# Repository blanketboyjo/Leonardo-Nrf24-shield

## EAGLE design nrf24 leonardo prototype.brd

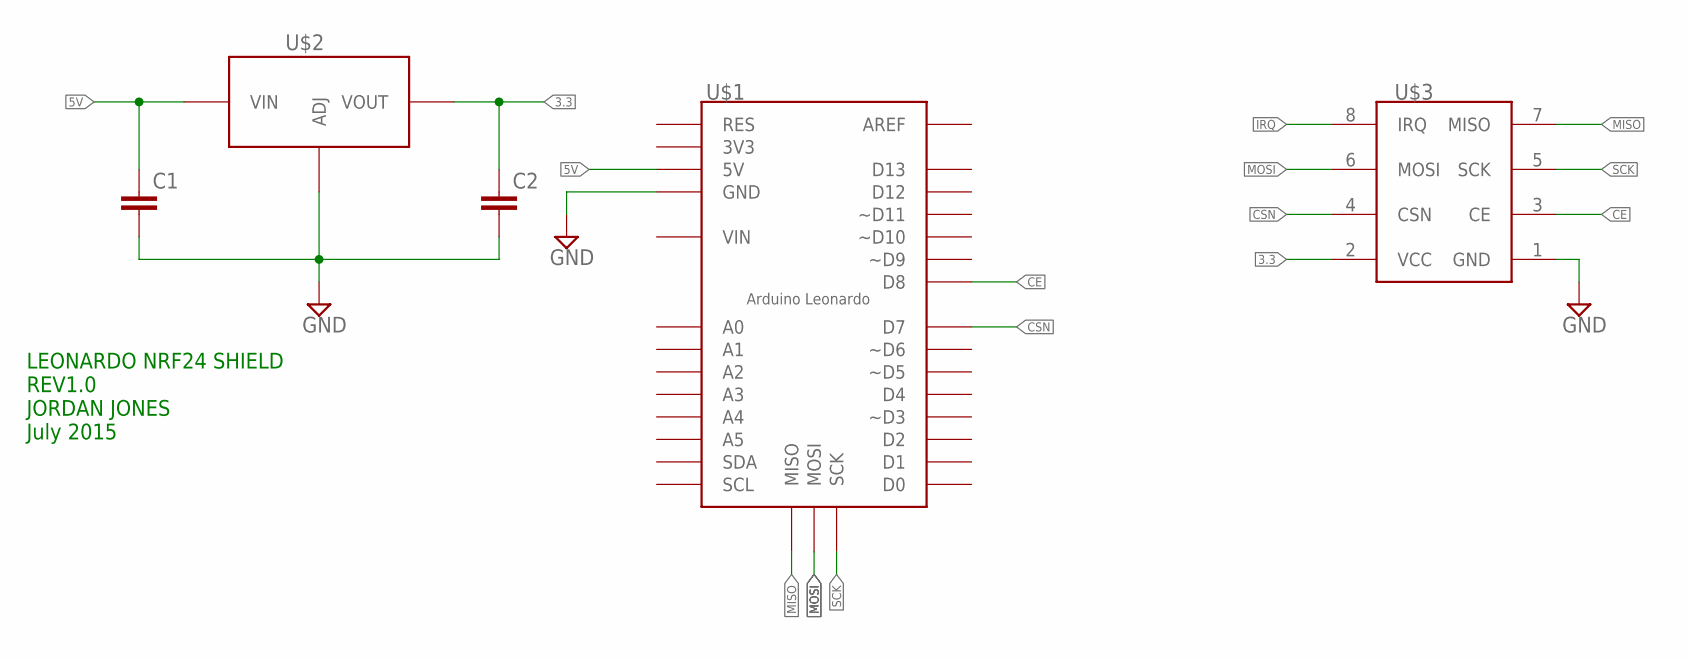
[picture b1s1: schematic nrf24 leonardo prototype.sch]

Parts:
C1, C2: CAP0603-CAP; 0603-CAP
U$1: LEONARDOSHIELDLEONARDO; ARDUINOSHIELDR3ISP
U$2: LM1117; SOT223
U$3: NRF24L01

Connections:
3.3: C2.1, U$2.P2 (VOUT), U$2.P4 (VOUT), U$3.2 (VCC)
5V: C1.1, U$1.5V1 (5V), U$1.5V2 (5V), U$2.P3 (VIN)
CE: U$1.D8, U$3.3 (CE)
CSN: U$1.D7, U$3.4 (CSN)
GND: C1.2, C2.2, U$1.GND1 (GND), U$1.GND2 (GND), U$1.GND3 (GND), U$1.GND4 (GND), U$2.P1 (ADJ), U$3.1 (GND)
IRQ: U$3.8 (IRQ)
MISO: U$1.MISO, U$3.7 (MISO)
MOSI: U$1.MOSI, U$3.6 (MOSI)
SCK: U$1.SCK, U$3.5 (SCK)

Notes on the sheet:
LEONARDO NRF24 SHIELD REV1.0 JORDAN JONES July 2015

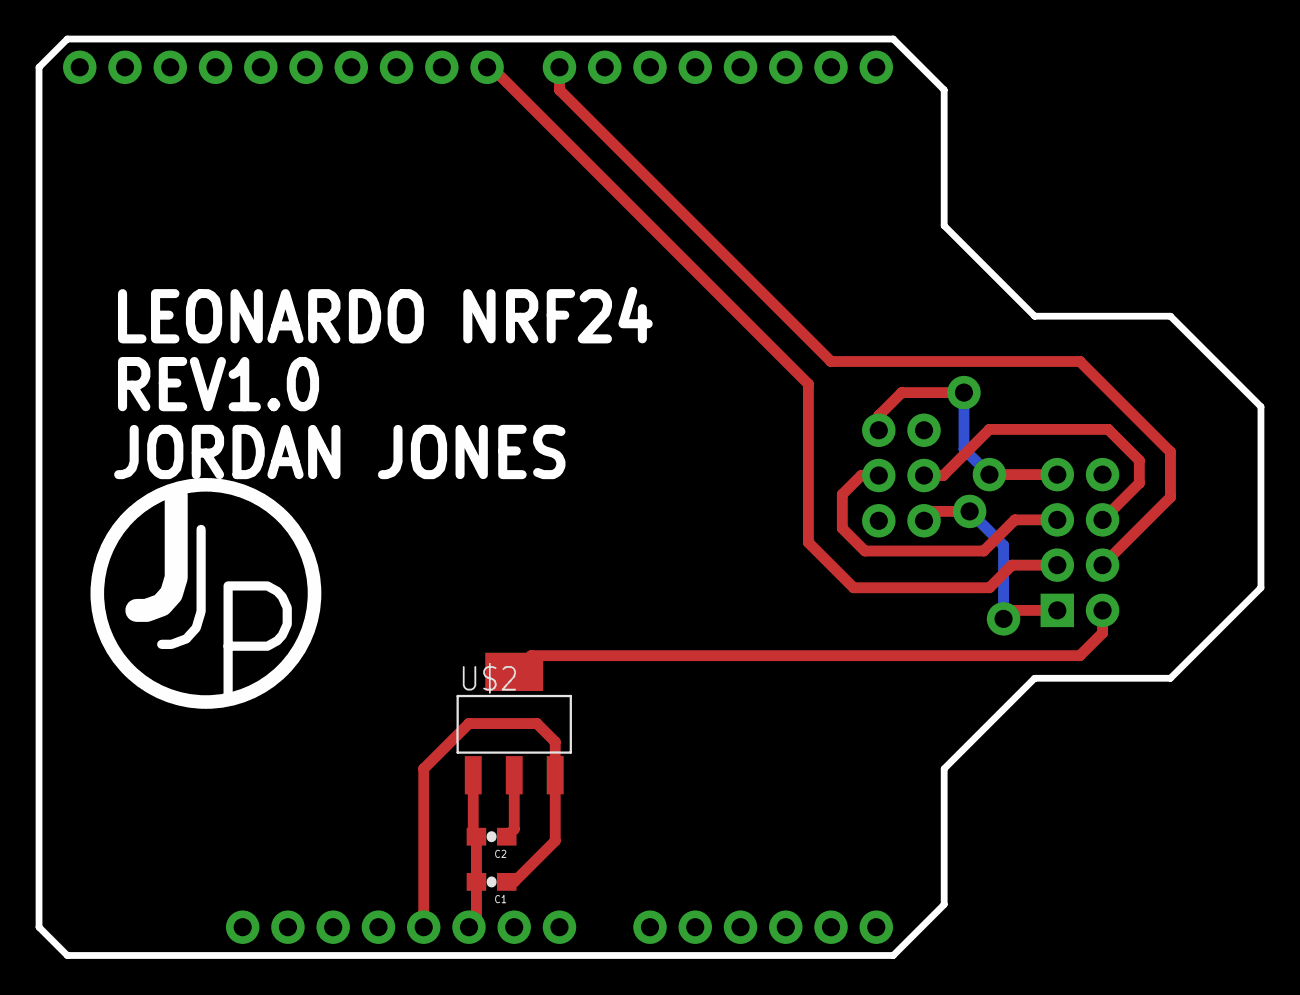
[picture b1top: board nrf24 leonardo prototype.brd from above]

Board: 2 copper layers, 68.2 x 51.1 mm, 5 parts (1 on the bottom side), 8 nets.

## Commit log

2015-07-15 :confetti_ball: Added .gitattributes & .gitignore files
2015-07-15 First upload
    Uploaded original board and updated ignore file to ignore eagle version
    control files
2015-07-15 Update
    Just moved a few things

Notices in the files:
parts and their libraries:
SparkFun-Capacitors: Licensing: Creative Commons ShareAlike 4.0 International - https://creativecommons.org/licenses/by-sa/4.0
